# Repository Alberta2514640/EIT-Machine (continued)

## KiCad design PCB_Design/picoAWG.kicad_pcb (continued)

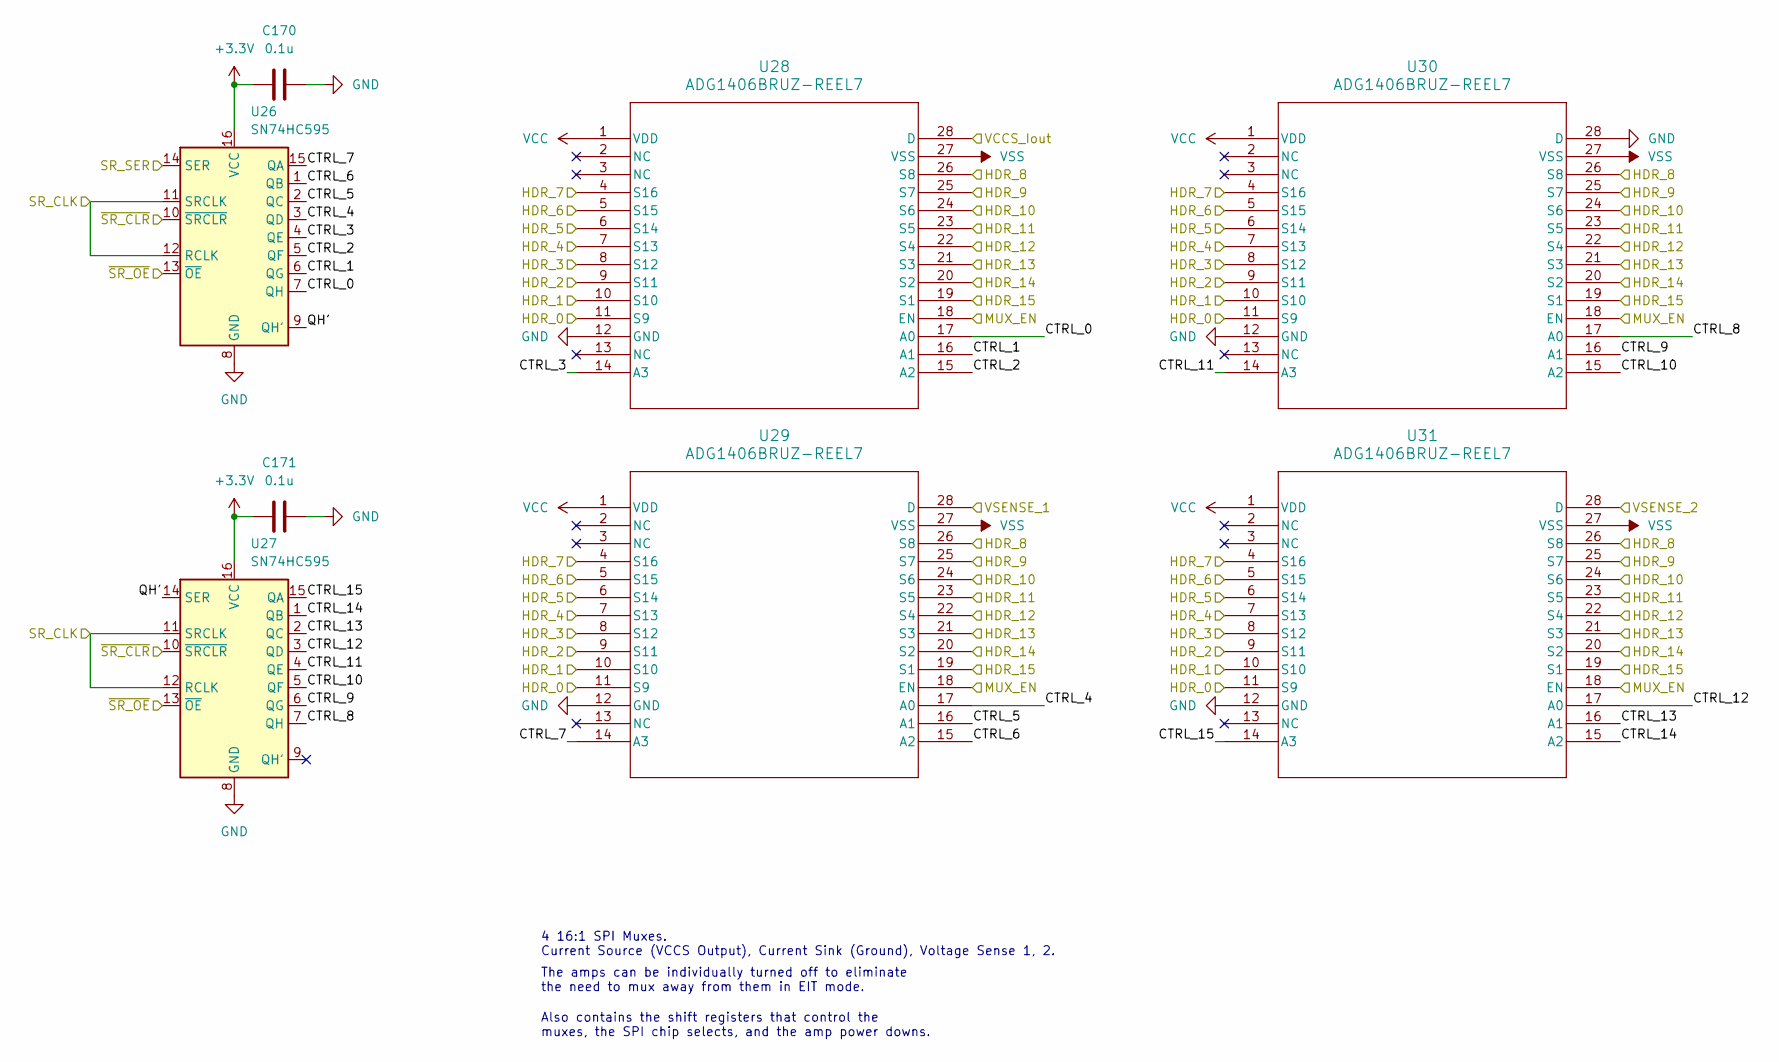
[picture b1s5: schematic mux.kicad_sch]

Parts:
C170, C171: 0.1u; C_0603_1608Metric
U26, U27: SN74HC595; SOIC-16W_5.3x10.2mm_P1.27mm
U28, U29, U30, U31: ADG1406BRUZ-REEL7; RU_28_ADI

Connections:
+3.3V: C170.1, C171.1, U26.16 (VCC), U27.16 (VCC); also elsewhere on the board
/Analog/SENSE_IN_1: U29.28 (D); also elsewhere on the board
/Analog/SENSE_IN_2: U31.28 (D); also elsewhere on the board
/HDR_0: U28.11 (S9), U29.11 (S9), U30.11 (S9), U31.11 (S9); also elsewhere on the board
/HDR_1: U28.10 (S10), U29.10 (S10), U30.10 (S10), U31.10 (S10); also elsewhere on the board
/HDR_2: U28.9 (S11), U29.9 (S11), U30.9 (S11), U31.9 (S11); also elsewhere on the board
/HDR_3: U28.8 (S12), U29.8 (S12), U30.8 (S12), U31.8 (S12); also elsewhere on the board
/HDR_4: U28.7 (S13), U29.7 (S13), U30.7 (S13), U31.7 (S13); also elsewhere on the board
/HDR_5: U28.6 (S14), U29.6 (S14), U30.6 (S14), U31.6 (S14); also elsewhere on the board
/HDR_6: U28.5 (S15), U29.5 (S15), U30.5 (S15), U31.5 (S15); also elsewhere on the board
/HDR_7: U28.4 (S16), U29.4 (S16), U30.4 (S16), U31.4 (S16); also elsewhere on the board
/HDR_8: U28.26 (S8), U29.26 (S8), U30.26 (S8), U31.26 (S8); also elsewhere on the board
/HDR_9: U28.25 (S7), U29.25 (S7), U30.25 (S7), U31.25 (S7); also elsewhere on the board
/HDR_10: U28.24 (S6), U29.24 (S6), U30.24 (S6), U31.24 (S6); also elsewhere on the board
/HDR_11: U28.23 (S5), U29.23 (S5), U30.23 (S5), U31.23 (S5); also elsewhere on the board
/HDR_12: U28.22 (S4), U29.22 (S4), U30.22 (S4), U31.22 (S4); also elsewhere on the board
/HDR_13: U28.21 (S3), U29.21 (S3), U30.21 (S3), U31.21 (S3); also elsewhere on the board
/HDR_14: U28.20 (S2), U29.20 (S2), U30.20 (S2), U31.20 (S2); also elsewhere on the board
/HDR_15: U28.19 (S1), U29.19 (S1), U30.19 (S1), U31.19 (S1); also elsewhere on the board
/MUX_EN: U28.18 (EN), U29.18 (EN), U30.18 (EN), U31.18 (EN); also elsewhere on the board
/Mux Control/CTRL_0: U26.7 (QH), U28.17 (A0)
/Mux Control/CTRL_1: U26.6 (QG), U28.16 (A1)
/Mux Control/CTRL_2: U26.5 (QF), U28.15 (A2)
/Mux Control/CTRL_3: U26.4 (QE), U28.14 (A3)
/Mux Control/CTRL_4: U26.3 (QD), U29.17 (A0)
/Mux Control/CTRL_5: U26.2 (QC), U29.16 (A1)
/Mux Control/CTRL_6: U26.1 (QB), U29.15 (A2)
/Mux Control/CTRL_7: U26.15 (QA), U29.14 (A3)
/Mux Control/CTRL_8: U27.7 (QH), U30.17 (A0)
/Mux Control/CTRL_9: U27.6 (QG), U30.16 (A1)
/Mux Control/CTRL_10: U27.5 (QF), U30.15 (A2)
/Mux Control/CTRL_11: U27.4 (QE), U30.14 (A3)
/Mux Control/CTRL_12: U27.3 (QD), U31.17 (A0)
/Mux Control/CTRL_13: U27.2 (QC), U31.16 (A1)
/Mux Control/CTRL_14: U27.1 (QB), U31.15 (A2)
/Mux Control/CTRL_15: U27.15 (QA), U31.14 (A3)
/Mux Control/QH': U26.9 (QH'), U27.14 (SER)
/SR_CLK: U26.11 (SRCLK), U26.12 (RCLK), U27.11 (SRCLK), U27.12 (RCLK); also elsewhere on the board
/SR_SER: U26.14 (SER); also elsewhere on the board
/VCCS_Iout: U28.28 (D); also elsewhere on the board
/~SR_CLR: U26.10 (~SRCLR), U27.10 (~SRCLR); also elsewhere on the board
/~SR_OE: U26.13 (~OE), U27.13 (~OE); also elsewhere on the board
GND: C170.2, C171.2, U26.8 (GND), U27.8 (GND), U28.12 (GND), U29.12 (GND), U30.12 (GND), U30.28 (D), U31.12 (GND); also elsewhere on the board
VCC: U28.1 (VDD), U29.1 (VDD), U30.1 (VDD), U31.1 (VDD); also elsewhere on the board
VSS: U28.27 (VSS), U29.27 (VSS), U30.27 (VSS), U31.27 (VSS); also elsewhere on the board

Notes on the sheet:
4 16:1 SPI Muxes. Current Source (VCCS Output), Current Sink (Ground), Voltage Sense 1, 2.
Also contains the shift registers that control the muxes, the SPI chip selects, and the amp power downs.
The amps can be individually turned off to eliminate the need to mux away from them in EIT mode.

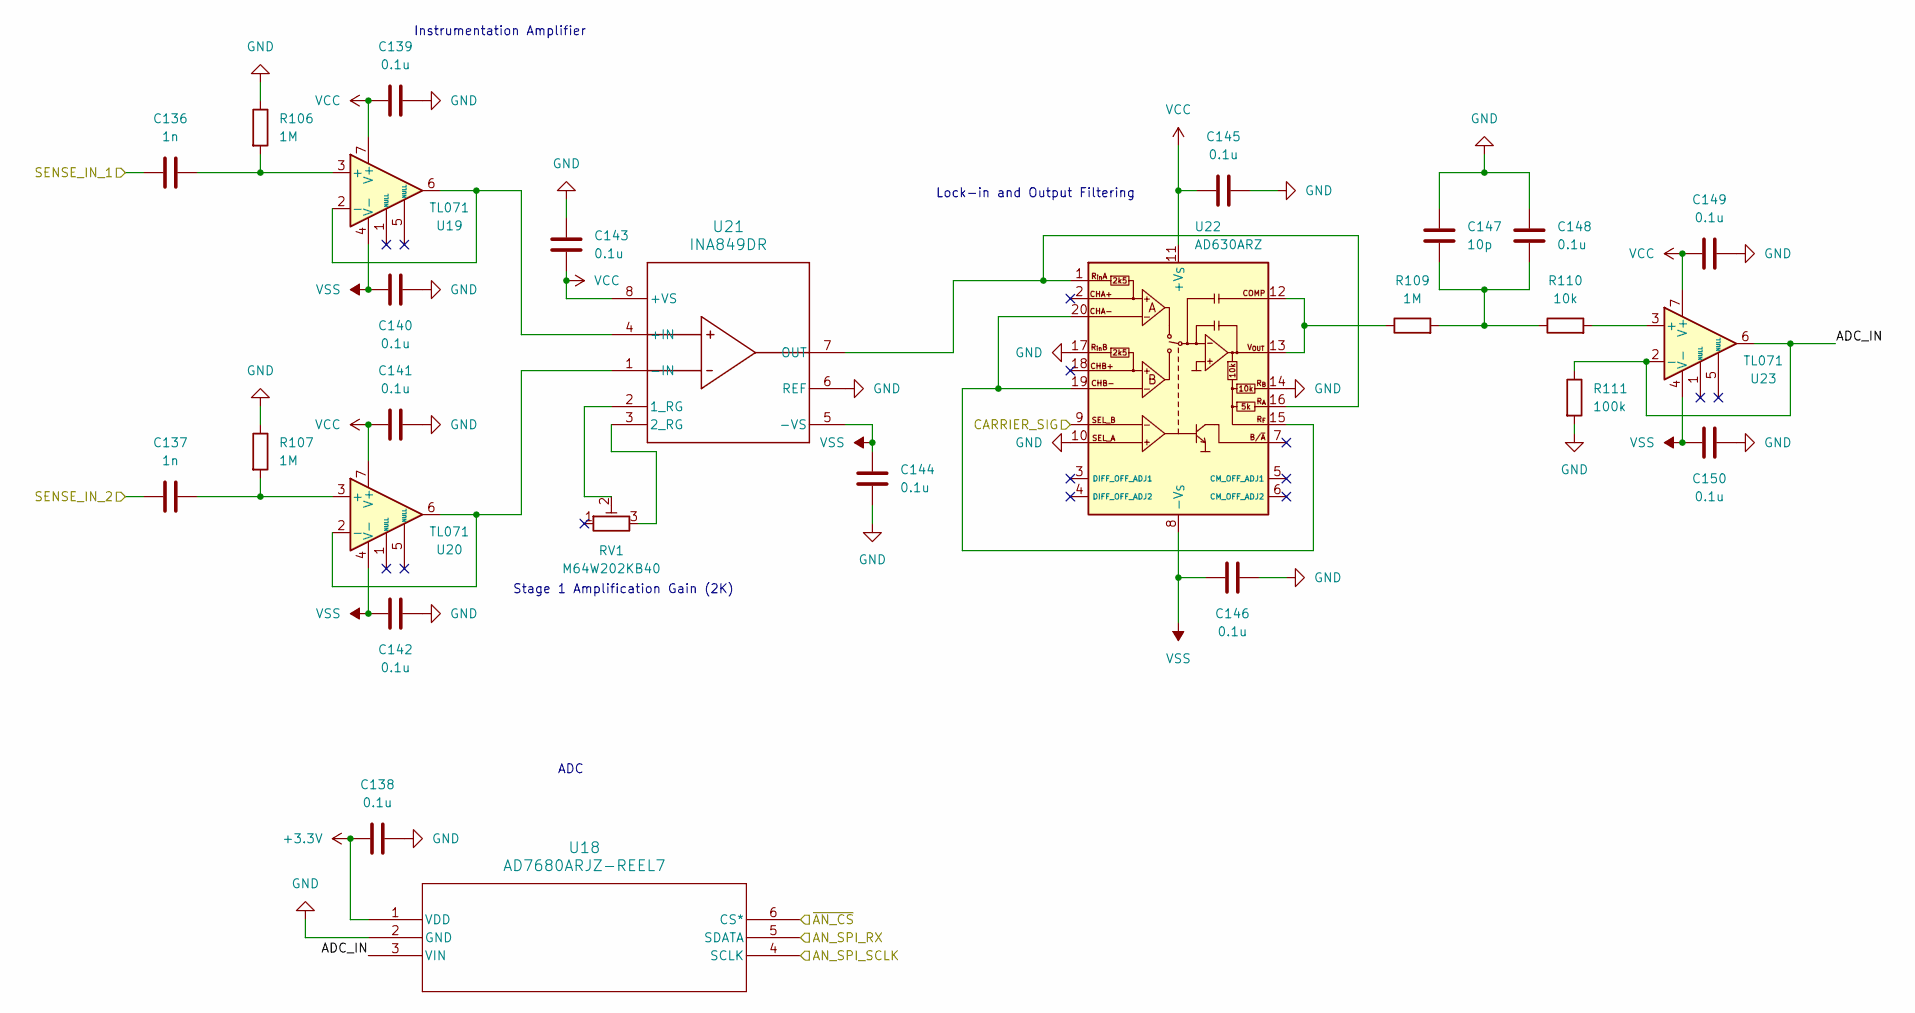
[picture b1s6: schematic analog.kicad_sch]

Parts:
C136, C137: 1n; C_0603_1608Metric
C138, C139, C140, C141, C142, C143, C144, C145, C146, C148, C149, C150: 0.1u; C_0603_1608Metric
C147: 10p; C_0603_1608Metric
R106, R107, R109: 1M; R_0603_1608Metric
R110: 10k; R_0603_1608Metric
R111: 100k; R_0603_1608Metric
RV1: M64W202KB40; POT_2023-08-01_VIS
U18: AD7680ARJZ-REEL7; RJ_6_ADI
U19, U20, U23: TL071; TSSOP-8_3x3mm_P0.65mm
U21: INA849DR; D0008A-IPC_A
U22: AD630ARZ; SOIC-20W_7.5x12.8mm_P1.27mm

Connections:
+3.3V: C138.1, U18.1 (VDD); also elsewhere on the board
/Analog/ADC_IN: R111.1, U18.3 (VIN), U23.2 (-), U23.6
/Analog/CARRIER_SIG: U22.9 (SEL_B); also elsewhere on the board
/Analog/SENSE_IN_1: C136.2; also elsewhere on the board
/Analog/SENSE_IN_2: C137.2; also elsewhere on the board
/SPI0_RX: U18.5 (SDATA); also elsewhere on the board
/SPI0_SCLK: U18.4 (SCLK); also elsewhere on the board
/~AN_CS: U18.6 (CS*); also elsewhere on the board
GND: C138.2, C139.2, C140.1, C141.2, C142.1, C143.2, C144.2, C145.1, C146.1, C147.1, C148.1, C149.2, C150.1, R106.1, R107.1, R111.2, U18.2 (GND), U21.6 (REF), U22.10 (SEL_A), U22.14 (R_{B}), U22.17 (R_{in}B); also elsewhere on the board
unnamed: C147.2, C148.2, R109.2, R110.1
unnamed: C136.1, R106.2, U19.3 (+)
unnamed: U19.2 (-), U19.6, U21.4 (+IN)
unnamed: C137.1, R107.2, U20.3 (+)
unnamed: U20.2 (-), U20.6, U21.1 (-IN)
unnamed: RV1.2, U21.2 (1_RG)
unnamed: RV1.3, U21.3 (2_RG)
unnamed: U21.7 (OUT), U22.1 (R_{in}A), U22.16 (R_{A})
unnamed: U22.15 (R_{F}), U22.19 (CHB-), U22.20 (CHA-)
unnamed: R109.1, U22.12 (COMP), U22.13 (V_{OUT})
unnamed: R110.2, U23.3 (+)
VCC: C139.1, C141.1, C143.1, C145.2, C149.1, U19.7 (V+), U20.7 (V+), U21.8 (+VS), U22.11 (+V_{S}), U23.7 (V+); also elsewhere on the board
VSS: C140.2, C142.2, C144.1, C146.2, C150.2, U19.4 (V-), U20.4 (V-), U21.5 (-VS), U22.8 (-V_{S}), U23.4 (V-); also elsewhere on the board

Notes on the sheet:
Lock-in and Output Filtering
Instrumentation Amplifier
ADC
Stage 1 Amplification Gain (2K)

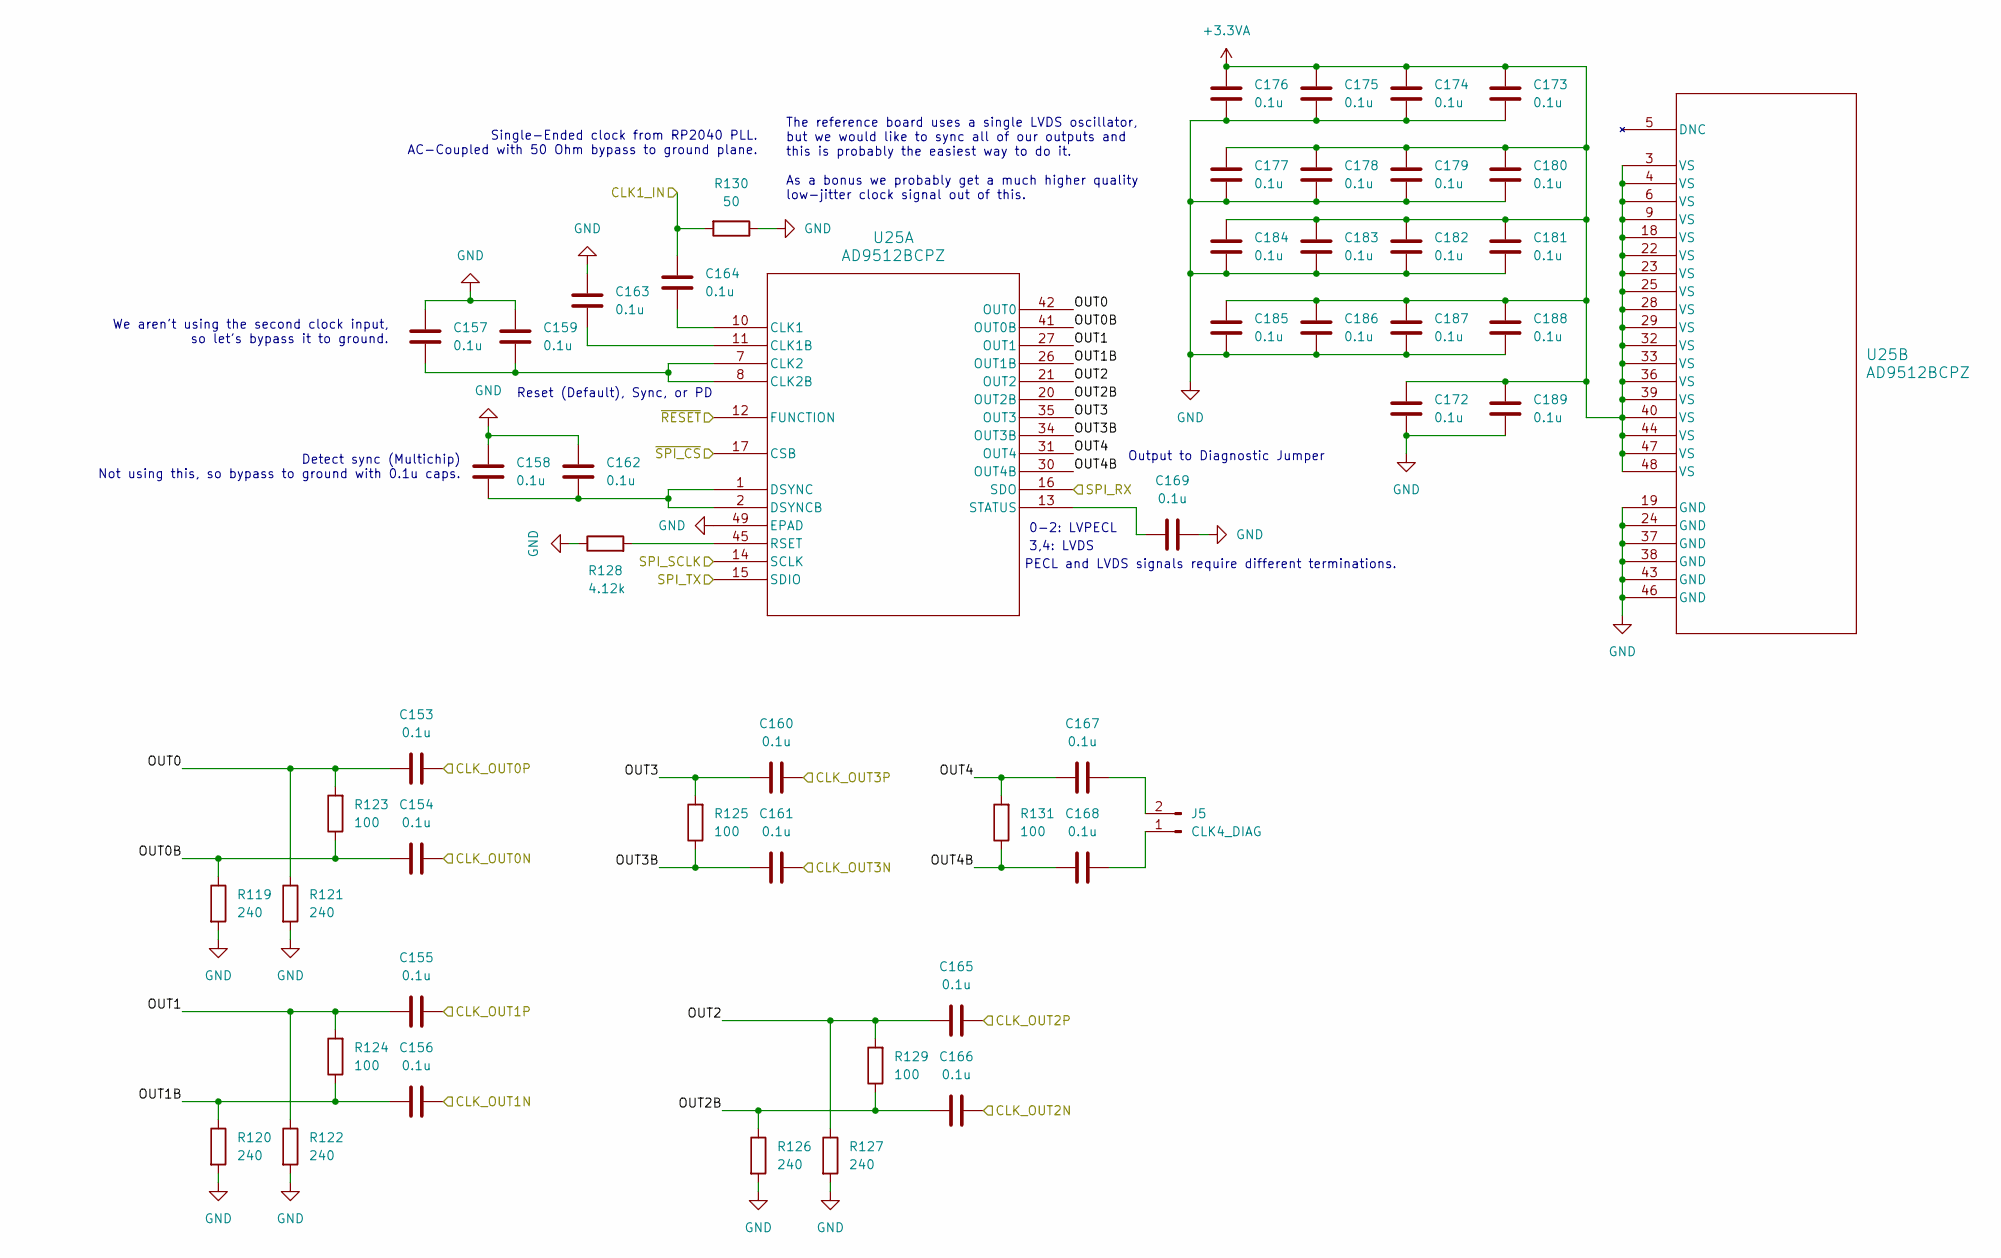
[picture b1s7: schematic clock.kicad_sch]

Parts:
C153, C154, C155, C156, C157, C158, C159, C160, C161, C162, C163, C164, C165, C166, C167, C168, C169, C172, C173, C174, C175, C176, C177, C178, C179, C180, C181, C182, C183, C184, C185, C186, C187, C188, C189: 0.1u; C_0603_1608Metric
J5: CLK4_DIAG; PinHeader_1x02_P2.54mm_Vertical
R119, R120, R121, R122, R126, R127: 240; R_0603_1608Metric
R123, R124, R125, R129, R131: 100; R_0603_1608Metric
R128: 4.12k; R_0603_1608Metric
R130: 50; R_0603_1608Metric
U25: AD9512BCPZ; CP_48_1_ADI

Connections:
+3.3VA: C172.1, C173.1, C174.1, C175.1, C176.1, C177.1, C178.1, C179.1, C180.1, C181.1, C182.1, C183.1, C184.1, C185.1, C186.1, C187.1, C188.1, C189.1, U25.3 (VS), U25.4 (VS), U25.6 (VS), U25.9 (VS), U25.18 (VS), U25.22 (VS), U25.23 (VS), U25.25 (VS), U25.28 (VS), U25.29 (VS), U25.32 (VS), U25.33 (VS), U25.36 (VS), U25.39 (VS), U25.40 (VS), U25.44 (VS), U25.47 (VS), U25.48 (VS); also elsewhere on the board
/CLK_0N: C154.2; also elsewhere on the board
/CLK_0P: C153.2; also elsewhere on the board
/CLK_1N: C156.2; also elsewhere on the board
/CLK_1P: C155.2; also elsewhere on the board
/CLK_2N: C166.2; also elsewhere on the board
/CLK_2P: C165.2; also elsewhere on the board
/CLK_3N: C161.2; also elsewhere on the board
/CLK_3P: C160.2; also elsewhere on the board
/Clock/OUT0: C153.1, R121.1, R123.2, U25.42 (OUT0)
/Clock/OUT0B: C154.1, R119.1, R123.1, U25.41 (OUT0B)
/Clock/OUT1: C155.1, R122.1, R124.2, U25.27 (OUT1)
/Clock/OUT1B: C156.1, R120.1, R124.1, U25.26 (OUT1B)
/Clock/OUT2: C165.1, R127.1, R129.2, U25.21 (OUT2)
/Clock/OUT2B: C166.1, R126.1, R129.1, U25.20 (OUT2B)
/Clock/OUT3: C160.1, R125.2, U25.35 (OUT3)
/Clock/OUT3B: C161.1, R125.1, U25.34 (OUT3B)
/Clock/OUT4: C167.1, R131.2, U25.31 (OUT4)
/Clock/OUT4B: C168.1, R131.1, U25.30 (OUT4B)
/SPI1_RX: U25.16 (SDO); also elsewhere on the board
/SPI1_SCLK: U25.14 (SCLK); also elsewhere on the board
/SPI1_TX: U25.15 (SDIO); also elsewhere on the board
/uC_CLKOUT: C164.1, R130.2; also elsewhere on the board
/~CLK_CS: U25.17 (CSB); also elsewhere on the board
/~RESET: U25.12 (FUNCTION); also elsewhere on the board
GND: C157.1, C158.2, C159.1, C162.2, C163.1, C169.1, C172.2, C173.2, C174.2, C175.2, C176.2, C177.2, C178.2, C179.2, C180.2, C181.2, C182.2, C183.2, C184.2, C185.2, C186.2, C187.2, C188.2, C189.2, R119.2, R120.2, R121.2, R122.2, R126.2, R127.2, R128.1, R130.1, U25.19 (GND), U25.24 (GND), U25.37 (GND), U25.38 (GND), U25.43 (GND), U25.46 (GND), U25.49 (EPAD); also elsewhere on the board
unnamed: C168.2, J5.1
unnamed: C167.2, J5.2
unnamed: C164.2, U25.10 (CLK1)
unnamed: C163.2, U25.11 (CLK1B)
unnamed: C157.2, C159.2, U25.7 (CLK2), U25.8 (CLK2B)
unnamed: C158.1, C162.1, U25.1 (DSYNC), U25.2 (DSYNCB)
unnamed: R128.2, U25.45 (RSET)
unnamed: C169.2, U25.13 (STATUS)

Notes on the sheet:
The reference board uses a single LVDS oscillator, but we would like to sync all of our outputs and this is probably the easiest way to do it. As a bonus we probably get a much higher quality low-jitter clock signal out of this.
PECL and LVDS signals require different terminations.
0-2: LVPECL
We aren't using the second clock input, so let's bypass it to ground.
Reset (Default), Sync, or PD
3,4: LVDS
Output to Diagnostic Jumper
Detect sync (Multichip) Not using this, so bypass to ground with 0.1u caps.
Single-Ended clock from RP2040 PLL. AC-Coupled with 50 Ohm bypass to ground plane.

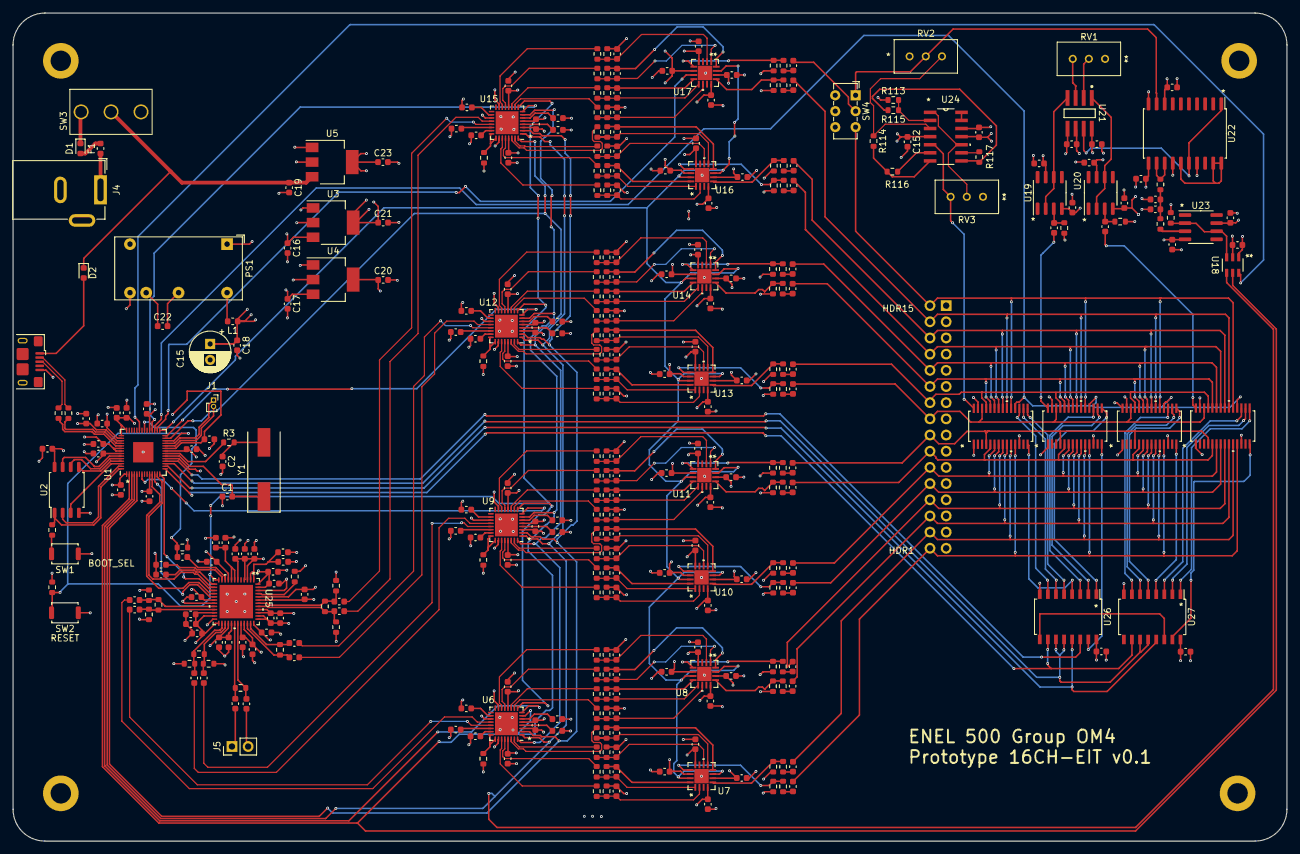
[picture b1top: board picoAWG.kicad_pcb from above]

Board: 4 copper layers, 200.0 x 130.0 mm, 366 parts (1 on the bottom side), 267 nets.

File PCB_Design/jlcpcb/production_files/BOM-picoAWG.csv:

Comment,Designator,Footprint,LCSC
SN74HC595,"U26,U27",SOIC-16W_5.3x10.2mm_P1.27mm,C10092
27p,"C1,C2",C_0603_1608Metric,C107045
BOOT_SEL,"SW1,SW2",SW_Push_SPST_NO_Alps_SKRK,C115357
629105150521,J2,USB_Micro-B_Amphenol_10118193-0001LF_Horizontal,C132562
0.1u,"C10,C100,C101,C102,C103,C108,C109,C11,C110,C115,C116,C117,C118,C119,C12,C124,C125,C126,C127,C128,C129,C13,C130,C131,C138,C139,C14,C140,C141,C142,C143,C144,C145,C146,C148,C149,C150,C151,C152,C153,C154,C155,C156,C157,C158,C159,C160,C161,C162,C163,C164,C165,C166,C167,C168,C169,C170,C171,C172,C173,C174,C175,C176,C177,C178,C179,C180,C181,C182,C183,C184,C185,C186,C187,C188,C189,C24,C25,C26,C3,C31,C32,C33,C34,C35,C40,C41,C42,C43,C44,C45,C46,C47,C5,C52,C53,C54,C59,C6,C60,C61,C62,C63,C68,C69,C70,C71,C72,C73,C74,C75,C8,C80,C81,C82,C87,C88,C89,C9,C90,C91,C96,C97,C98,C99",C_0603_1608Metric,C14663
NCP1117-3.3_SOT223,"U3,U4",SOT-223-3_TabPin2,C146799
1u,"C104,C105,C106,C107,C132,C133,C134,C135,C4,C48,C49,C50,C51,C7,C76,C77,C78,C79",C_0603_1608Metric,C15849
1n,"C136,C137",C_0603_1608Metric,C1588
F0603E1R25FSTR,F1,Fuse_0603_1608Metric,C163109
10p,C147,C_0603_1608Metric,C1634
NCP1117-5.0_SOT223,U5,SOT-223-3_TabPin2,C185806
10u,"C16,C17,C19,C20,C21,C22,C23",C_0603_1608Metric,C19702
RP2040,U1,QFN-56-1EP_7x7mm_P0.4mm_EP3.2x3.2mm,C2040
OPA4228UA,U24,D14,C2060814
1k,"R100,R101,R113,R114,R115,R23,R24,R25,R26,R3,R4,R48,R49,R50,R51,R73,R74,R75,R76,R98,R99",R_0603_1608Metric,C21190
470u,C15,CP_Radial_D6.3mm_P2.50mm,C217537
100,"R123,R124,R125,R129,R131",R_0603_1608Metric,C22775
1M,"R106,R107,R109",R_0603_1608Metric,C22935
499,"R10,R11,R116,R117,R12,R13,R14,R15,R16,R17,R18,R19,R20,R21,R31,R32,R33,R34,R35,R36,R37,R38,R39,R40,R41,R42,R43,R44,R45,R46,R56,R57,R58,R59,R6,R60,R61,R62,R63,R64,R65,R66,R67,R68,R69,R7,R70,R71,R8,R81,R82,R83,R84,R85,R86,R87,R88,R89,R9,R90,R91,R92,R93,R94,R95,R96",R_0603_1608Metric,C23065
4.7k,R5,R_0603_1608Metric,C23162
49.9,"R102,R103,R104,R105,R27,R28,R29,R30,R52,R53,R54,R55,R77,R78,R79,R80",R_0603_1608Metric,C23185
240,"R119,R120,R121,R122,R126,R127",R_0603_1608Metric,C23350
2.2u,C18,C_0603_1608Metric,C23630
100k,R111,R_0603_1608Metric,C25803
10k,R110,R_0603_1608Metric,C25804
INA849DR,U21,D0008A-IPC_A,C2871861
8.06K,"R22,R47,R72,R97",R_0603_1608Metric,C2984365
27.4,"R1,R2",R_0603_1608Metric,C403125
1.5p,"C111,C112,C113,C114,C120,C121,C122,C123,C27,C28,C29,C30,C36,C37,C38,C39,C55,C56,C57,C58,C64,C65,C66,C67,C83,C84,C85,C86,C92,C93,C94,C95",C_0603_1608Metric,C5186670
TL071HD,"U19,U20,U23",SOIC-8_3.9x4.9mm_P1.27mm,C5214234
PMEG3020CEP,"D1,D2",D_0603_1608Metric,C552871
18u,L1,L_0603_1608Metric,C57839
AD7680ARJZ-REEL7,U18,RJ_6_ADI,C578463
ADA4817-2ACPZ-R7,"U10,U11,U13,U14,U16,U17,U7,U8",CP_16_4_ADI,C578929
ABLS-12.000MHZ-B4-T,Y1,Crystal_SMD_HC49-SD,C596818
AD630ARZ,U22,SOIC-20W_7.5x12.8mm_P1.27mm,C650378
AD9106BCP,"U12,U15,U6,U9",LFCSP-32-1EP_5x5mm_P0.5mm_EP3.6x3.6mm,C653186
AD9512BCPZ,U25,CP_48_1_ADI,C653489
ADG1406BRUZ-REEL7,"U28,U29,U30,U31",RU_28_ADI,C654796
4.12k,R128,R_0603_1608Metric,C723644
50,R130,R_0603_1608Metric,C849792
W25Q128JVS,U2,SOIC-8_5.23x5.23mm_P1.27mm,C97521

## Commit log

2023-03-31 PCB Design Added
2023-03-31 Added RP2040 Code
2023-04-01 added new functions
2023-04-01 basic app setup
2023-04-01 Added Sliders for Sine Square Triangle
2023-04-01 Writing to the DAC functions
2023-04-01 Final Comitt of the Day
2023-04-03 changed default register
2023-04-03 fixed some writes still nto able to probe
2023-04-04 added a read register and read the output register
2023-04-04 increased clock speed to 50mhz
2023-04-05 Added Enclosure Design
2023-04-05 expended readme TODO Slightly
2023-05-24 added some additional helper functions and docs
2024-01-09 Change PCB to KiCAD
    Basic project framework. PCB design coming in future commits
2024-01-09 Add datasheets (DAC, Pico)
2024-02-09 Schematic v1
2024-02-10 Added Mesh View Button To GUI
2024-03-01 KiCAD file update, completed PCB
2024-03-03 Slight board updates - Added board PDFs and images
2024-03-04 Added the GUI code
2024-03-04 Rename app.py to app(unused).py
    Renamed to add the tag unused to avoid confusion
2024-03-05 Final KiCAD Files Submitted to JLC PCB
2024-03-10 Added pictures of GUI design and Figma mockup
2024-03-15 Updated Meshes
2024-03-20 Updated datasheets
2024-03-20 Embedded software initial commit
2024-03-20 Updated PCB Board Images
2024-03-20 Cleanup KiCAD .gitignore
2024-03-20 Cleanup KiCAD project folder
2024-03-20 Cleanup .gitignore
2024-03-22 Remove KiCAD Temp files
2024-03-25 Added more serial communication, code cleaning
    Added more serial communication to parameter changing and setting preset waves, and cleaned up some of the code that was unneeded.
2024-03-25 Fixed space, added serial for mode swapping
    Fixed the space that occurred when switching back from EIT mode to AWG mode, added serial communication when swapping to EIT mode and vice-versa
2024-03-26 Added code for RP2040 for communicating with GUI
2024-03-26 PCB Gitignore and PDF
2024-03-26 Embedded Update
2024-03-27 Shift Register Code
2024-03-27 ADC Embedded Code (Not Tested)
2024-03-27 Wave generation Jupyter Notebook for debug
2024-03-28 [03/27/2024] Cleaned up code, Added comments, Added exception for serial connection
    Removed some unnecessary code, added some comments that was missing and added an exception for serial connection
2024-03-28 Removed unused GUI files in this branch
2024-03-28 wavegen.py : Generates graph data
2024-03-28 Embedded Updates March27
2024-03-28 Added some functionality, Improved EIT Interface, Added Exception handling for parameter input
2024-03-28 [03/27/2024]Reverting commit
    Reverting commit that unintentionally deleted some files
2024-03-28 [03/27/2024] Small changes to EIT
    added proper units for the parameters in EIT
2024-03-28 Small adjustments to EIT interface
    Added submit button for EIT, resized the EIT display
2024-03-28 [03/27/2024] Added more formal documentation, Code cleanup
    Added more proper documentation and mode parameter was unused for the draw_window function.
2024-03-28 Added EIT implementation notes
2024-03-29 [03/28/2024] Removed Voltages from EIT Interface, Made Changes to AWG interface
    AWG:
    - Fixed ranges for the spin elements for the parameters
    -Re-added mode, mistake of deleting it earlier
    - Reorganized some of the code to have the global variables at the top
2024-03-29 [03/28/2024] Additional Cleanup of code
2024-03-29 Removed awg.py (Functionality rolled into ad9106.py)
2024-03-29 Implementation comments for embedded
2024-03-29 [03/29/2024] Added parameter bound checking, error popups
    Added parameter bound checking for Amplitude, Frequency, and Phase.
    Added error popups for when input(s) are invalid.
    Fixed default parameters for the channels
2024-03-30 Fixed some main.py typing issues. Removed serial in main.py as they will be implemented in user_serial.py
2024-03-30 Added user_serial.py to handle serial between the RP2040 and the computer
2024-03-30 Bugfixes. Added new wave types: cosine, sawtooth up, sawtooth down
2024-03-30 Removed redundant type conversion functions
2024-04-01 Adjusted shift register baud
2024-04-01 Removed eit.py, as its functionality was rolled into user_serial.py
2024-04-01 Very minor AD9106 comment adjustment
2024-04-01 Removed redundant function
2024-04-01 Added EIT graphing functionality
2024-04-02 Adjust size of window to avoid squishing EIT graph
2024-04-02 Wait for serial ack before sending more
2024-04-02 Fixed AD7680 bugs
2024-04-02 Barebones AD9106 initialization
2024-04-02 Enforce zero timeout on data COM port
2024-04-02 Add SPI debug code. Added COM ack for port control
2024-04-02 Support iterating over excitations and measurement pairs
2024-04-02 Janky SN74HC595 extra cycle fix
2024-04-02 Actual janky SN74HC595 fix
